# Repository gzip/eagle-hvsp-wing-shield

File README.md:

# HVSP Wing Shield

Ever accidently brick your ATtiny device by setting the fuse bits incorrectly? Or maybe you want to reclaim the reset pin and ditch the bootloader. High Voltage Serial Programming (HVSP) to the rescue. This circuit provides a small Arduino shield that enables you to rescue your 8-pin ATtiny devices from the junk box. There's also a version for ATtiny so they can rescue eachother.

See [Fuse Recovery](docs/FuseRecovery.md) for the various ways that fuses settings can lock out ISP programming.

## 12V Supply Requirement
In High Voltage Serial Programming, "high voltage" refers to 12V, which is well above the ATtiny's typical 5V operation. Common 12V supplies include wall adapters, generic USB boost converters that can be connected in various ways, and standard 12V batteries such as 23A/A23 cells.

## Programming from ATtiny

This shield was originally designed to work with an Arduino, but it can now also work with ATtiny devices. See [ATtiny Instructions](attiny/README.md) for more details.

# Availability

Boards available at [OSH Park](https://www.oshpark.com/shared_projects/0LHEovb9).

Kits available at [Tindie](https://www.tindie.com/products/gzip/avr-attiny-rescue-kit-hvsp-wing-shield-for-arduino/).

# Credit

Original Arduino sketch provided by [Rickety](http://www.rickety.us/2010/03/arduino-avr-high-voltage-serial-programmer/). ATtiny version assited by Antigravity.

# License

The hardware is licensed under [Creative Commons Share Alike](http://creativecommons.org/licenses/by-sa/4.0/). The Arduino sketch provides no explicit license.

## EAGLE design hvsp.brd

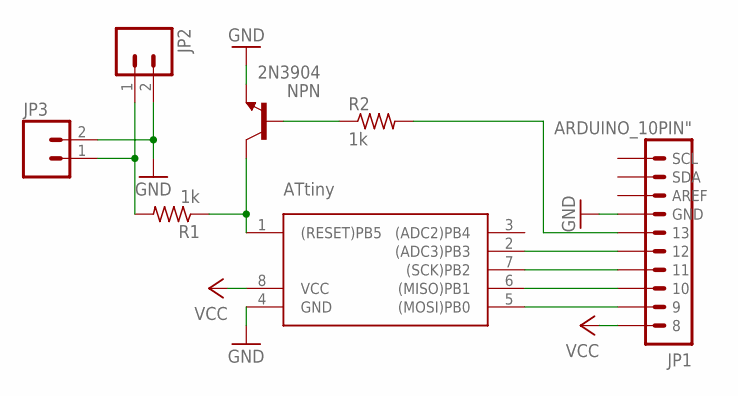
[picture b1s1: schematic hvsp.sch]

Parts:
JP1: ARDUINO_10PIN"; ARDUINO_10PIN
JP2: M025MM; SCREWTERMINAL-5MM-2
JP3: M021X02_NO_SILK; 1X02_NO_SILK
NPN: 2N3904; TO92
R1, R2: 1k; 0204/7
U$2: ATtiny; AVR-7_DIL08

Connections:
GND: JP1.4 (GND), JP2.2, JP3.2, NPN.3 (E), U$2.4 (GND)
unnamed: NPN.2 (B), R2.1
unnamed: JP2.1, JP3.1, R1.2
unnamed: JP1.6 (12), U$2.2 ((ADC3)PB3)
unnamed: JP1.7 (11), U$2.7 ((SCK)PB2)
unnamed: JP1.8 (10), U$2.6 ((MISO)PB1)
unnamed: JP1.9, U$2.5 ((MOSI)PB0)
unnamed: JP1.5 (13), R2.2
unnamed: NPN.1 (C), R1.1, U$2.1 ((RESET)PB5)
VCC: JP1.10 (8), U$2.8 (VCC)

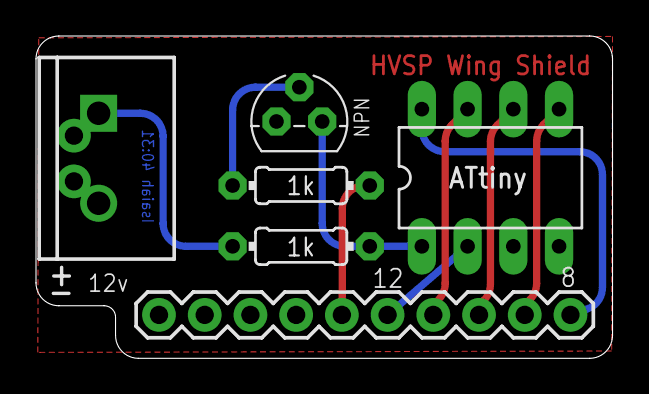
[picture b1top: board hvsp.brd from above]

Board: 2 copper layers, 32.0 x 17.9 mm, 7 parts (0 on the bottom side), 10 nets.

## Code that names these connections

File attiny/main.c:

#define F_CPU 1000000UL  // 1 MHz internal oscillator (factory default with CKDIV8)

// Suppress false-positive -Warray-bounds warning emitted by GCC 12+ on AVR I/O register dereferencing
#pragma GCC diagnostic ignored "-Warray-bounds"

#include <avr/io.h>
#include <avr/power.h>
#include <util/delay.h>
#include <avr/sleep.h>
#include <stdint.h>

// Factory default fuse configuration for ATtiny25/45/85:
// HFUSE = 0xDF (SPIEN=0, BOD disabled, RST enabled)
// LFUSE = 0x62 (Internal 8MHz RC oscillator with CKDIV8 = 1MHz default)
#define HFUSE 0xDF
#define LFUSE 0x62

/*
 * Pin bit definitions on PORTB of programmer ATtiny85:
 *
 * Right Side (JP2 Header) -> Shield Pins 8, 9, 10:
 *   PB0 (Pin 5 / JP2 Pin 4) -> Shield Pin 10 (SII - Serial Instruction Input)
 *   PB1 (Pin 6 / JP2 Pin 3) -> Shield Pin 9  (SDI - Serial Data Input)
 *   PB2 (Pin 7 / JP2 Pin 2) -> Shield Pin 8  (Target Switched VCC)
 *
 * (Shield Pin 11 is SDO - Serial Data Output, unused in blind mode)
 *
 * Left Side (JP1 Header) -> Shield Pins 12, 13, 14:
 *   PB3 (Pin 2 / JP1 Pin 2) -> Shield Pin 12 (SCI - Serial Clock Input)
 *   PB4 (Pin 3 / JP1 Pin 3) -> Shield Pin 13 (HV_RST - 2N3904 12V Trigger)
 *   PB5 (Pin 1)             -> Programmer Reset (Kept as standard ISP Reset)
 */
#define INSTOUT     PB0
#define DATAOUT     PB1
#define TARGET_VCC  PB2
#define CLKOUT      PB3
#define HV_RST      PB4

static inline void clock_pulse(void) {
    _delay_us(10);
    PORTB |= (1 << CLKOUT);
    _delay_us(10);
    PORTB &= ~(1 << CLKOUT);
    _delay_us(10);
}

static void send_frame(uint8_t data, uint8_t instr) {
    // Start bit: SDI = 0, SII = 0, clock pulse
    PORTB &= ~((1 << DATAOUT) | (1 << INSTOUT));
    clock_pulse();

    // 8 data & instruction bits (MSB first)
    for (int8_t i = 7; i >= 0; i--) {
        if (data & (1 << i)) {
            PORTB |= (1 << DATAOUT);
        } else {
            PORTB &= ~(1 << DATAOUT);
        }

        if (instr & (1 << i)) {
            PORTB |= (1 << INSTOUT);
        } else {
            PORTB &= ~(1 << INSTOUT);
        }

        clock_pulse();
    }

    // End bits: SDI = 0, SII = 0, two clock pulses
    PORTB &= ~((1 << DATAOUT) | (1 << INSTOUT));
    clock_pulse();
    clock_pulse();
}

int main(void) {
    // Force internal clock prescaler to divide-by-8 (1 MHz system clock).
    // Guarantees F_CPU timing matches 1 MHz regardless of whether the
    // programmer's CKDIV8 fuse is programmed (0x62) or unprogrammed (0xE2).
    clock_prescale_set(clock_div_8);

    // 1. Configure all 5 pins as outputs
    DDRB |= (1 << TARGET_VCC) | (1 << HV_RST) | (1 << CLKOUT) | (1 << DATAOUT) | (1 << INSTOUT);

    // Initial idle state:
    //    Target VCC OFF (0V),
    //    HV_RST HIGH (2N3904 is turned ON, pulling Target RESET to 0V / 12V supply cut),
    //    All other signals LOW
    PORTB = (1 << HV_RST);
    _delay_ms(50);

    // Enter High-Voltage Serial Programming (HVSP) mode:
    //    a) Apply VCC (4.5V - 5.5V)
    //    b) Wait 20 - 60 us (Datasheet tVHV: min 20us, max 60us)
    //    c) Apply 12V to RESET (HV_RST LOW shuts off 2N3904, pulling RESET to 12V)
    //    d) Hold for at least 10 us (tHVRST) and wait 300us for internal stabilization
    PORTB |= (1 << TARGET_VCC);
    _delay_us(40);
    PORTB &= ~(1 << HV_RST);
    _delay_us(10);
    _delay_us(300);

    // Write High Fuse (HFUSE = 0xDF)
    send_frame(0x40, 0x4C);
    send_frame(HFUSE, 0x2C);
    send_frame(0x00, 0x74);
    send_frame(0x00, 0x7C);
    _delay_ms(30);  // Allow plenty of time for charge pump burn (datasheet max 4.5ms)

    // Write Low Fuse (LFUSE = 0x62)
    send_frame(0x40, 0x4C);
    send_frame(LFUSE, 0x2C);
    send_frame(0x00, 0x64);
    send_frame(0x00, 0x6C);
    _delay_ms(30);

    // Exit Programming Mode safely
    PORTB &= ~((1 << CLKOUT) | (1 << DATAOUT) | (1 << INSTOUT));
    PORTB |= (1 << HV_RST);       // Cut 12V from RESET
    _delay_us(40);
    PORTB &= ~(1 << TARGET_VCC);  // Cut Target VCC

    // Halt CPU in deep power-down sleep until next power cycle or reset
    set_sleep_mode(SLEEP_MODE_PWR_DOWN);
    sleep_enable();
    sleep_cpu();

    while (1) {
        // Fallback halt
    }
}

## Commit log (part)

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2014-11-18 Add gerbers readme
2014-11-26 Add link to oshpark

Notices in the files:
parts and their libraries:
SparkFun-Connectors: Licensing: Creative Commons ShareAlike 4.0 International - https://creativecommons.org/licenses/by-sa/4.0
